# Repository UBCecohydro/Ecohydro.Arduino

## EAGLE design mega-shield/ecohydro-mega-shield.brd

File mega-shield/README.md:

This is the UBC EcoHydro shield used in Costa Rica in 2015.

The version shown here is revised to remove some errors, it has not been sent to production yet.

RELEASE NOTES

Pending changes
- Add 2032 battery to BoM

Rev 1.5
- Add fiducials

Rev 1.4
- Reduced board size by 2mm to fit 10x10 economy pcb mfg

Rev 1.3 - Changes made but not yet tested in production
- Thermal, regulator gets hot when 5V @ 150mA

Rev 1.2 - Changes made but not yet tested in production
- Change R19 to 4k7
- GSM shield bypass pins are out by 1 (should be 2 & 3, not 3 & 4)
- Change pads on Batt and Solar connectors
- Change package on xtal
- Change C7 to 10V

Rev 1.1 - Changes made but not yet tested in production
- R19 change to 0805
- Transistor pinout was incorrect, fixed
- Should be using mega pins 8-15, not pins 7-14 (Not all pins on the Mega and Mega 2560 support change interrupts, so only the following can be used for RX: 10, 11, 12, 13, 14, 15, 50, 51, 52, 53, A8 (62), A9 (63), A10 (64), A11 (65), A12 (66), A13 (67), A14 (68), A15 (69).)
- DS1306 interrupt should be on pin 20 not pin 5
- label fuses

Rev 1.0 Costa Rica 2015
- Working

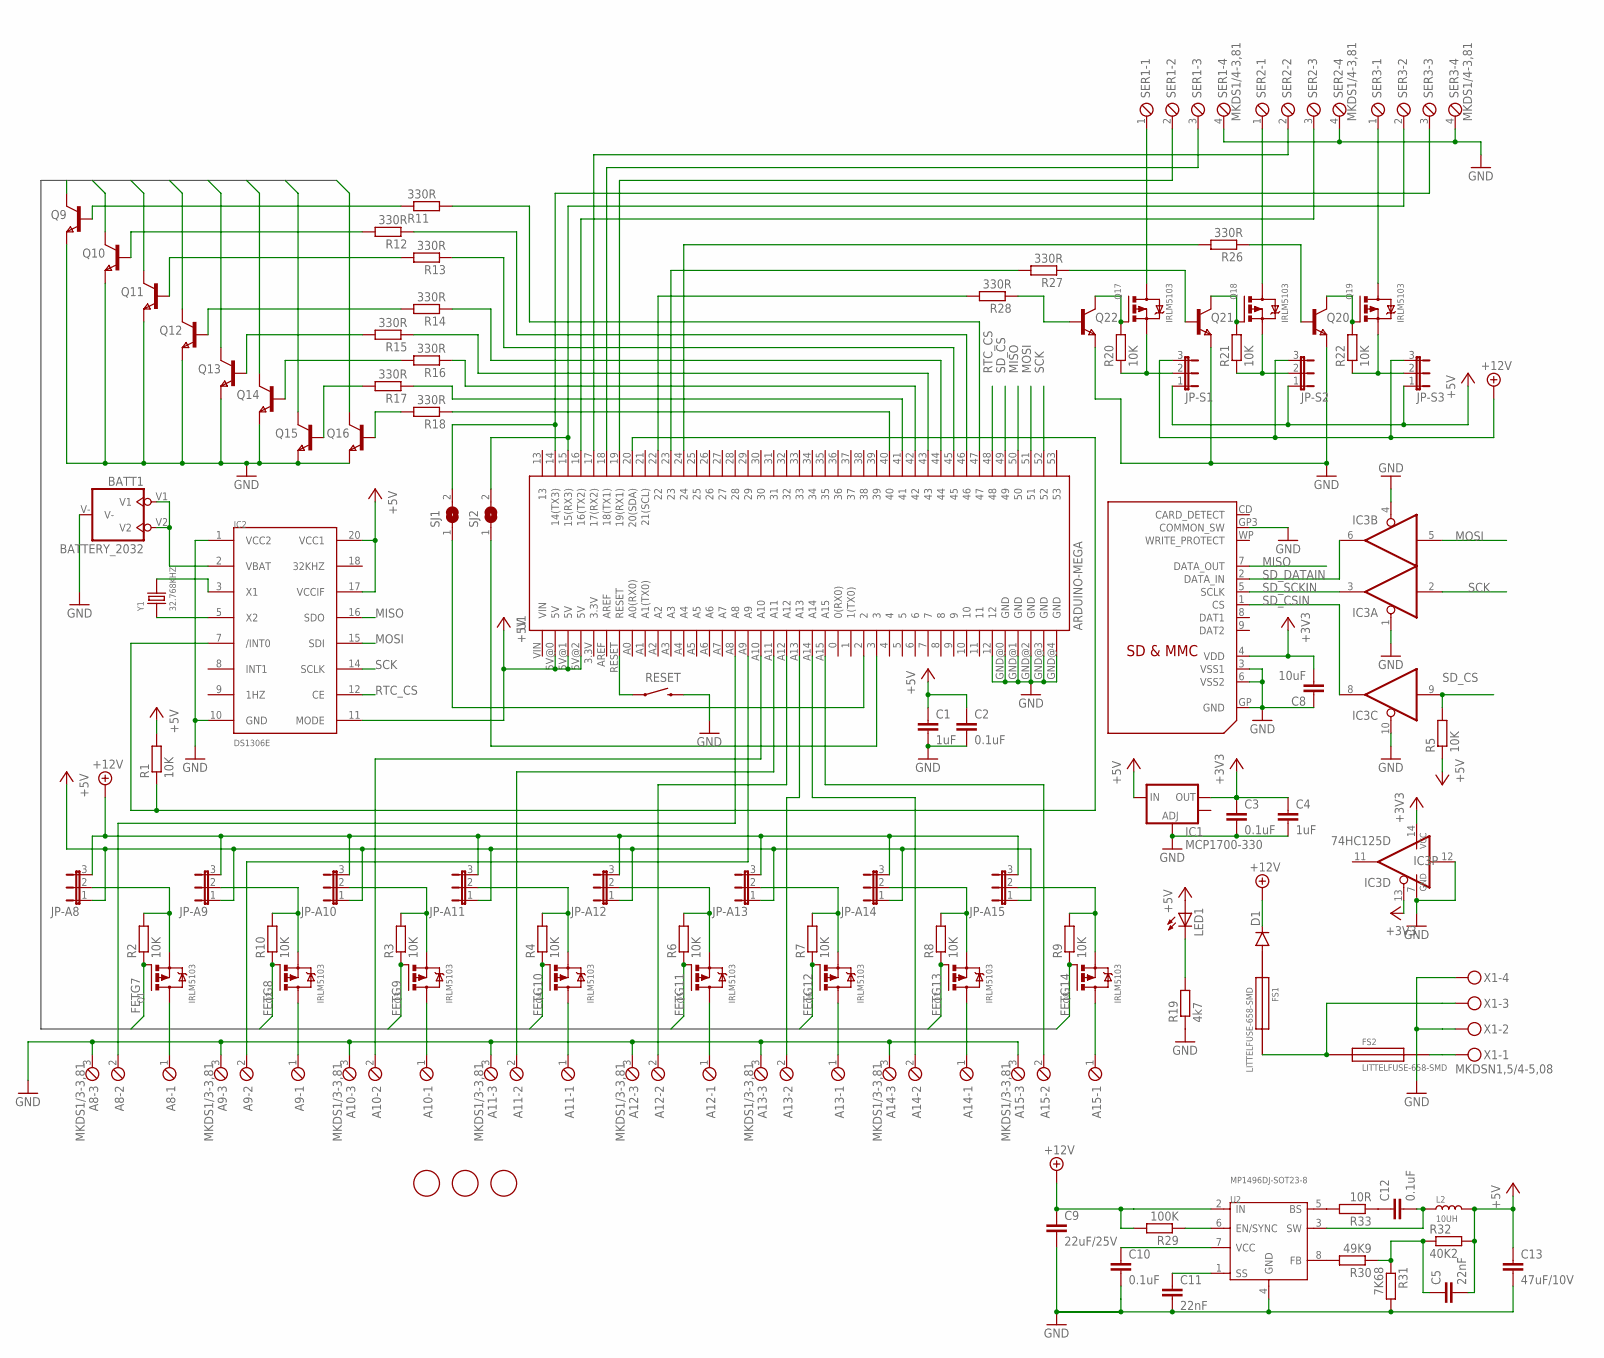
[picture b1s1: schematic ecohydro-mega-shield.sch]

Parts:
A8, A9, A10, A11, A12, A13, A14, A15: MKDS1/3-3,81; 3POL381
BATT1: BATTERY_2032; BATT2032; DIGIKEY BK-883CT-ND
C1, C4: 1uF; C0805K
C2, C3, C10, C12: 0.1uF; C0805K
C5, C11: 22nF; C0805K
C8: 10uF; C0805K
C9: 22uF/25V; C0805K; DIGIKEY 1276-2891-1-ND
C13: 47uF/10V; C0805K; DIGIKEY 709-1231-1-ND
D1: DIODESMA; SMA-DIODE; DIGIKEY S1GFSCT-ND
FS1, FS2: LITTELFUSE-658-SMD; MOUSER 576-65800001109
IC1: MCP1700-330; SOT223; DIGIKEY AP1117IE33G-13DITR-ND
IC2: DS1306E; SSOP20; DIGIKEY DS1306EN+T&RCT-ND
IC3: 74HC125D; SO14; DIGIKEY 568-1392-2-ND
JP-A8, JP-A9, JP-A10, JP-A11, JP-A12, JP-A13, JP-A14, JP-A15: JP2E; JP2
JP-S1, JP-S2, JP-S3: JP2E; JP2
L2: 10UH; SMD-2P-L6.0XW6.0XH3.0MM; DIGIKEY 732-5536-1-ND
LED1: LED1206; LED-1206
Q1, Q2, Q3, Q4, Q5, Q6, Q7, Q8, Q17, Q18, Q19: IRLM5103; MICRO3
Q9, Q10, Q11, Q12, Q13, Q14, Q15, Q16, Q20, Q21, Q22: PBSS4021NT,215; SOT23; DIGIKEY PBSS4021NT,215
R1, R2, R3, R4, R5, R6, R7, R8, R9, R10, R20, R21, R22: 10K; M0805
R11, R12, R13, R14, R15, R16, R17, R18: 330R; M0805; DIGIKEY 541-330ACT-ND
R19: 4k7; R0805
R26, R27, R28: 330R; M0805
R29: 100K; M0805
R30: 49K9; M0805; DIGIKEY 541-49.9KCCT-ND
R31: 7K68; M0805; DIGIKEY 541-49.9KCCT-ND
R32: 40K2; M0805; DIGIKEY 541-49.9KCCT-ND
R33: 10R; M0805; DIGIKEY 541-49.9KCCT-ND
RESET: SWITCH-MOMENTARY-2-SMD-1101NE; TACTILE-SWITCH-1101NE
SER1, SER2, SER3: MKDS1/4-3,81; 4POL381
SJ1, SJ2: SJ
U1: ARDUINO-MEGA; ARDUINO_MEGA_NOHOLES
U2: MP1496DJ-SOT23-8; SOT-23-8
U$1: SDMMC06132; 06132
U$2, U$3, U$4: FIDUCIAL; FIDUCIAL_1MM
X1: MKDSN1,5/4-5,08
Y1: 32.768KHZ; X2-SMD-L2.0X1.2X0.55MM; DIGIKEY 535-12051-1-ND

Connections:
+3V3: C3.1, C4.1, C8.2, IC1.2 (OUT), IC3.13 (OE), IC3.14 (VCC), U$1.4 (VDD)
+5V: C1.1, C2.1, C5.2, C13.1, IC1.3 (IN), IC2.11 (MODE), IC2.17 (VCCIF), IC2.20 (VCC1), JP-A8.1, JP-A9.1, JP-A10.1, JP-A11.1, JP-A12.1, JP-A13.1, JP-A14.1, JP-A15.1, JP-S1.1, JP-S2.1, JP-S3.1, L2.2, LED1.A, R1.2, R5.1, R32.2, U1.5V@0 (5V), U1.5V@1 (5V), U1.5V@2 (5V)
+12V: C9.1, D1.C, JP-A8.3, JP-A9.3, JP-A10.3, JP-A11.3, JP-A12.3, JP-A13.3, JP-A14.3, JP-A15.3, JP-S1.3, JP-S2.3, JP-S3.3, R29.2, U2.2 (IN)
+12VRAW: D1.A, FS1.1
FETG7: Q1.1 (G), Q16.3 (C), R2.1
FETG8: Q2.1 (G), Q15.3 (C), R10.1
FETG9: Q3.1 (G), Q14.3 (C), R3.1
FETG10: Q4.1 (G), Q13.3 (C), R4.1
FETG11: Q5.1 (G), Q12.3 (C), R6.1
FETG12: Q6.1 (G), Q11.3 (C), R7.1
FETG13: Q7.1 (G), Q10.3 (C), R8.1
FETG14: Q8.1 (G), Q9.3 (C), R9.1
GND: A8.3, A9.3, A10.3, A11.3, A12.3, A13.3, A14.3, A15.3, BATT1.V-, C1.2, C2.2, C3.2, C4.2, C8.1, C9.2, C10.2, C11.2, C13.2, IC1.1 (ADJ), IC2.1 (VCC2), IC2.10 (GND), IC3.1 (OE), IC3.4 (OE), IC3.7 (GND), IC3.10 (OE), IC3.12 (I), Q9.2 (E), Q10.2 (E), Q11.2 (E), Q12.2 (E), Q13.2 (E), Q14.2 (E), Q15.2 (E), Q16.2 (E), Q20.2 (E), Q21.2 (E), Q22.2 (E), R19.1, R31.2, RESET.P$2 (2), SER1.4, SER2.4, SER3.4, U1.12, U1.GND@0 (GND), U1.GND@1 (GND), U1.GND@2 (GND), U1.GND@3 (GND), U1.GND@4 (GND), U2.4 (GND), U$1.3 (VSS1), U$1.6 (VSS2), U$1.GP (GND), U$1.GP3 (COMMON_SW), X1.2, X1.4
MISO: IC2.16 (SDO), U1.50, U$1.7 (DATA_OUT)
MOSI: IC2.15 (SDI), IC3.5 (I), U1.51
unnamed: IC2.5 (X2), Y1.1
unnamed: RESET.P$1 (1), U1.RESET
unnamed: IC2.3 (X1), Y1.2
unnamed: A8.1, Q1.3 (D)
unnamed: A8.2, U1.A8
unnamed: A9.1, Q2.3 (D)
unnamed: A9.2, U1.A9
unnamed: A10.1, Q3.3 (D)
unnamed: A15.1, Q8.3 (D)
unnamed: A14.1, Q7.3 (D)
unnamed: A13.1, Q6.3 (D)
unnamed: A12.1, Q5.3 (D)
unnamed: A11.1, Q4.3 (D)
unnamed: IC2.7 (/INT0), R1.1, U1.20 (20(SDA))
unnamed: BATT1.V1, BATT1.V2, IC2.2 (VBAT)
unnamed: JP-A8.2, Q1.2 (S), R2.2
unnamed: A10.2, U1.A10
unnamed: A11.2, U1.A11
unnamed: JP-A10.2, Q3.2 (S), R3.2
unnamed: A12.2, U1.A12
unnamed: JP-A15.2, Q8.2 (S), R9.2
unnamed: JP-A14.2, Q7.2 (S), R8.2
unnamed: JP-A13.2, Q6.2 (S), R7.2
unnamed: JP-A12.2, Q5.2 (S), R6.2
unnamed: JP-A11.2, Q4.2 (S), R4.2
unnamed: JP-A9.2, Q2.2 (S), R10.2
unnamed: Q11.1 (B), R13.2
unnamed: Q12.1 (B), R14.2
unnamed: Q13.1 (B), R15.2
unnamed: A13.2, U1.A13
unnamed: Q14.1 (B), R16.2
unnamed: Q15.1 (B), R17.2
unnamed: Q16.1 (B), R18.2
unnamed: Q9.1 (B), R11.1
unnamed: Q10.1 (B), R12.2
unnamed: R11.2, U1.47
unnamed: R12.1, U1.46
unnamed: R13.1, U1.45
unnamed: R14.1, U1.44
unnamed: R15.1, U1.43
unnamed: R16.1, U1.42
unnamed: R17.1, U1.41
unnamed: R18.1, U1.40
unnamed: FS1.2, FS2.1, X1.3
unnamed: FS2.2, X1.1
unnamed: SER1.3, U1.18 (18(TX1))
unnamed: SER1.2, U1.19 (19(RX1))
unnamed: SER2.2, U1.17 (17(RX2))
unnamed: SER2.3, U1.16 (16(TX2))
unnamed: SER3.2, SJ2.2, U1.15 (15(RX3))
unnamed: SER3.3, SJ1.2, U1.14 (14(TX3))
unnamed: LED1.C, R19.2
unnamed: Q17.3 (D), SER1.1
unnamed: Q18.3 (D), SER2.1
unnamed: Q19.3 (D), SER3.1
unnamed: Q17.1 (G), Q22.3 (C), R20.2
unnamed: Q18.1 (G), Q21.3 (C), R21.2
unnamed: Q19.1 (G), Q20.3 (C), R22.2
unnamed: JP-S1.2, Q17.2 (S), R20.1
unnamed: JP-S2.2, Q18.2 (S), R21.1
unnamed: JP-S3.2, Q19.2 (S), R22.1
unnamed: Q20.1 (B), R26.1
unnamed: R26.2, U1.24
unnamed: Q21.1 (B), R27.1
unnamed: R27.2, U1.23
unnamed: Q22.1 (B), R28.1
unnamed: R28.2, U1.22
unnamed: C10.1, U2.7 (VCC)
unnamed: SJ2.1, U1.3
unnamed: R29.1, U2.6 (EN/SYNC)
unnamed: C11.1, U2.1 (SS)
unnamed: SJ1.1, U1.2
unnamed: R30.2, U2.8 (FB)
unnamed: C5.1, R30.1, R31.1, R32.1
unnamed: C12.2, L2.1, U2.3 (SW)
unnamed: R33.2, U2.5 (BS)
unnamed: C12.1, R33.1
unnamed: A14.2, U1.A14
unnamed: A15.2, U1.A15
RTC_CS: IC2.12 (CE), U1.48
SCK: IC2.14 (SCLK), IC3.2 (I), U1.52
SD_CS: IC3.9 (I), R5.2, U1.49
SD_CSIN: IC3.8 (O), U$1.1 (CS)
SD_DATAIN: IC3.6 (O), U$1.2 (DATA_IN)
SD_SCKIN: IC3.3 (O), U$1.5 (SCLK)

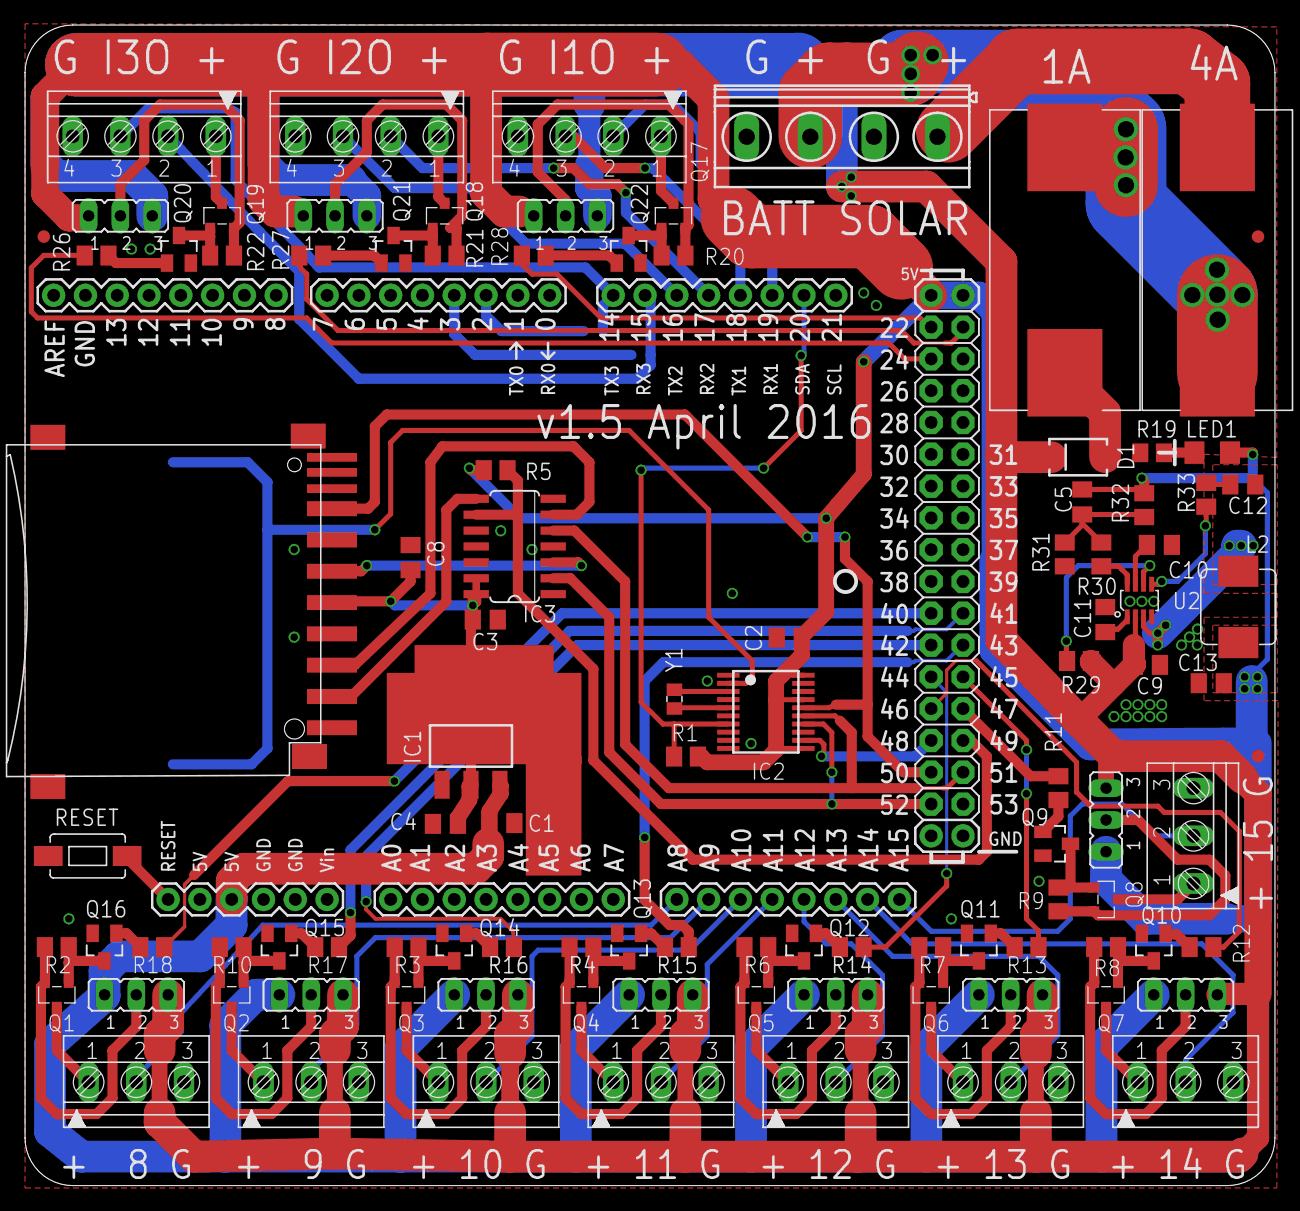
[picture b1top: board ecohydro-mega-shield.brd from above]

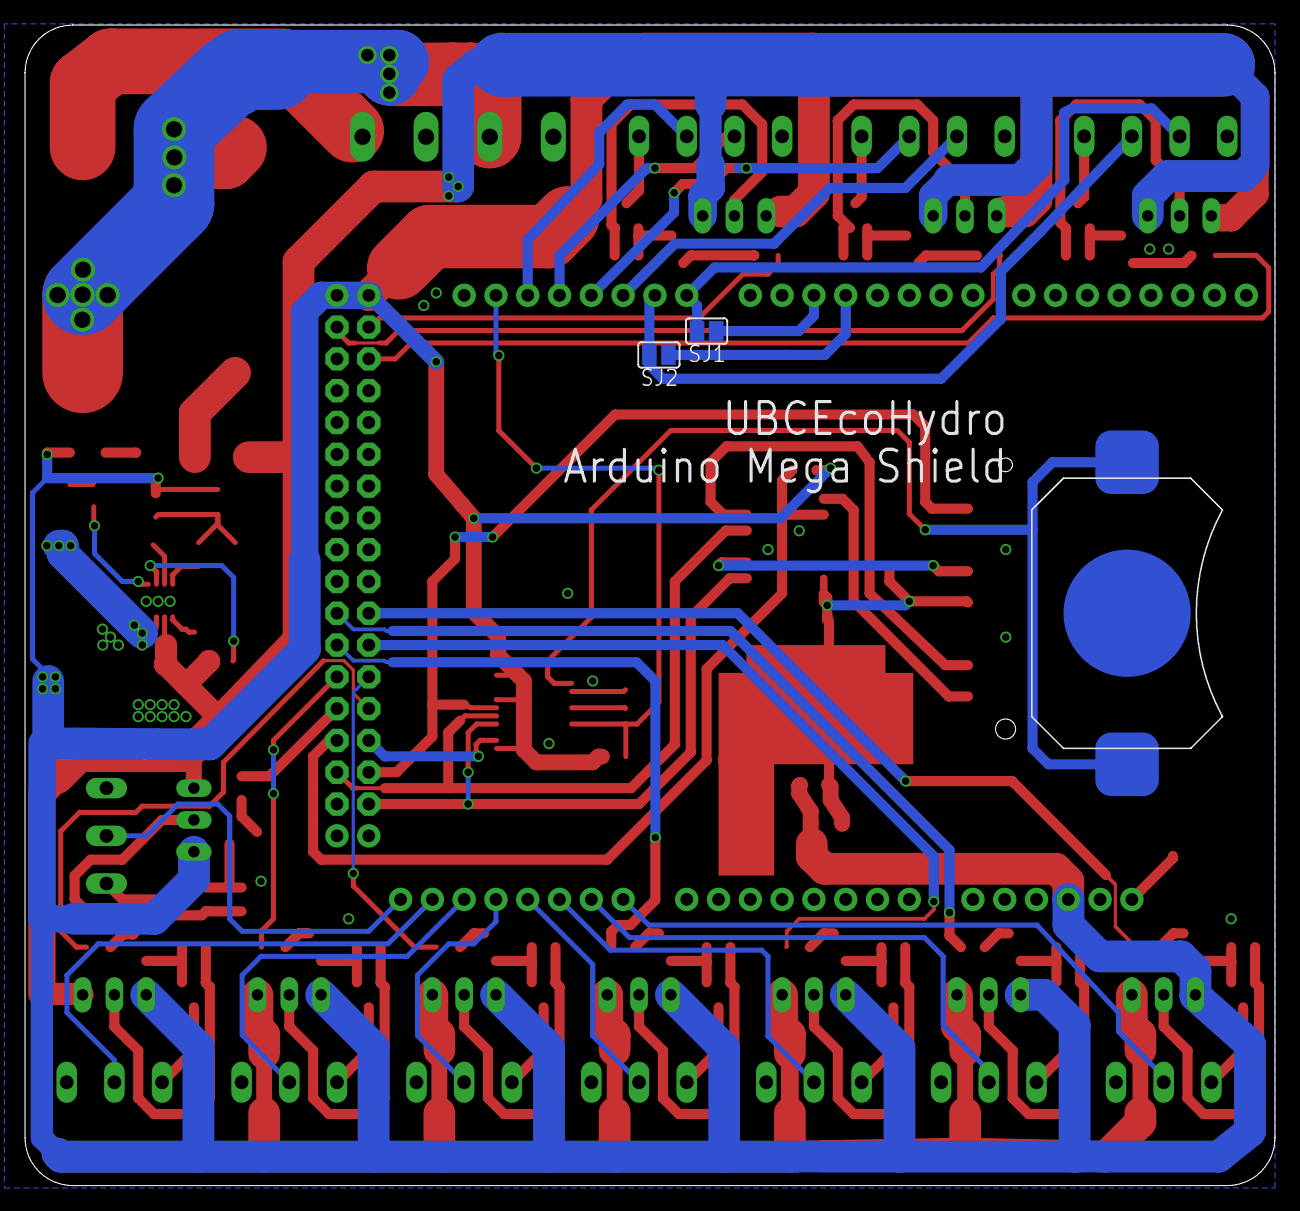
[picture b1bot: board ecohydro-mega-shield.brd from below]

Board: 2 copper layers, 99.8 x 92.7 mm, 105 parts (3 on the bottom side), 100 nets.

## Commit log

2016-02-27 Updated version with release notes
2016-02-27 Fixed formatting
2016-02-27 clarified wording
2016-02-28 Added files via upload
2016-02-29 Add schematic image
2016-02-29 Tidy images
2016-02-29 Cleaned up pcb image
2016-03-01 Added files via upload
    Arduino Protocol for programming Ecohydro Logger to query SDI-sensor data and record it on SD card
2016-03-01 Added files via upload
    Arduino protocol for setting time on Ecohydro Logger
2016-04-05 Placing sketches into folder
2016-04-05 Added gerbers for rev 1.0
2016-04-06 Rev 1.1 with some fixes, not sent for production yet
2016-04-06 Rev 1.2 Fixes - Change R19 to 4k7 - GSM shield bypass pins are out by 1 (should be 2 & 3, not 3 & 4) - Change pads on Batt and Solar connectors - Change package on xtal
2016-04-06 Add BoM
2016-04-06 Updated C7 voltage
2016-04-08 Rev 1.4 - Reduced board size by 2mm to fit 10x10 economy pcb mfg
2016-04-10 Rev 1.5 - Add fiducials
2016-04-10 Added missing rev 1.3
2016-04-15 Fix designators on power select jumpers

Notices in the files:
parts and their libraries:
SparkFun-PowerIC: Licensing: Creative Commons ShareAlike 4.0 International - https://creativecommons.org/licenses/by-sa/4.0
